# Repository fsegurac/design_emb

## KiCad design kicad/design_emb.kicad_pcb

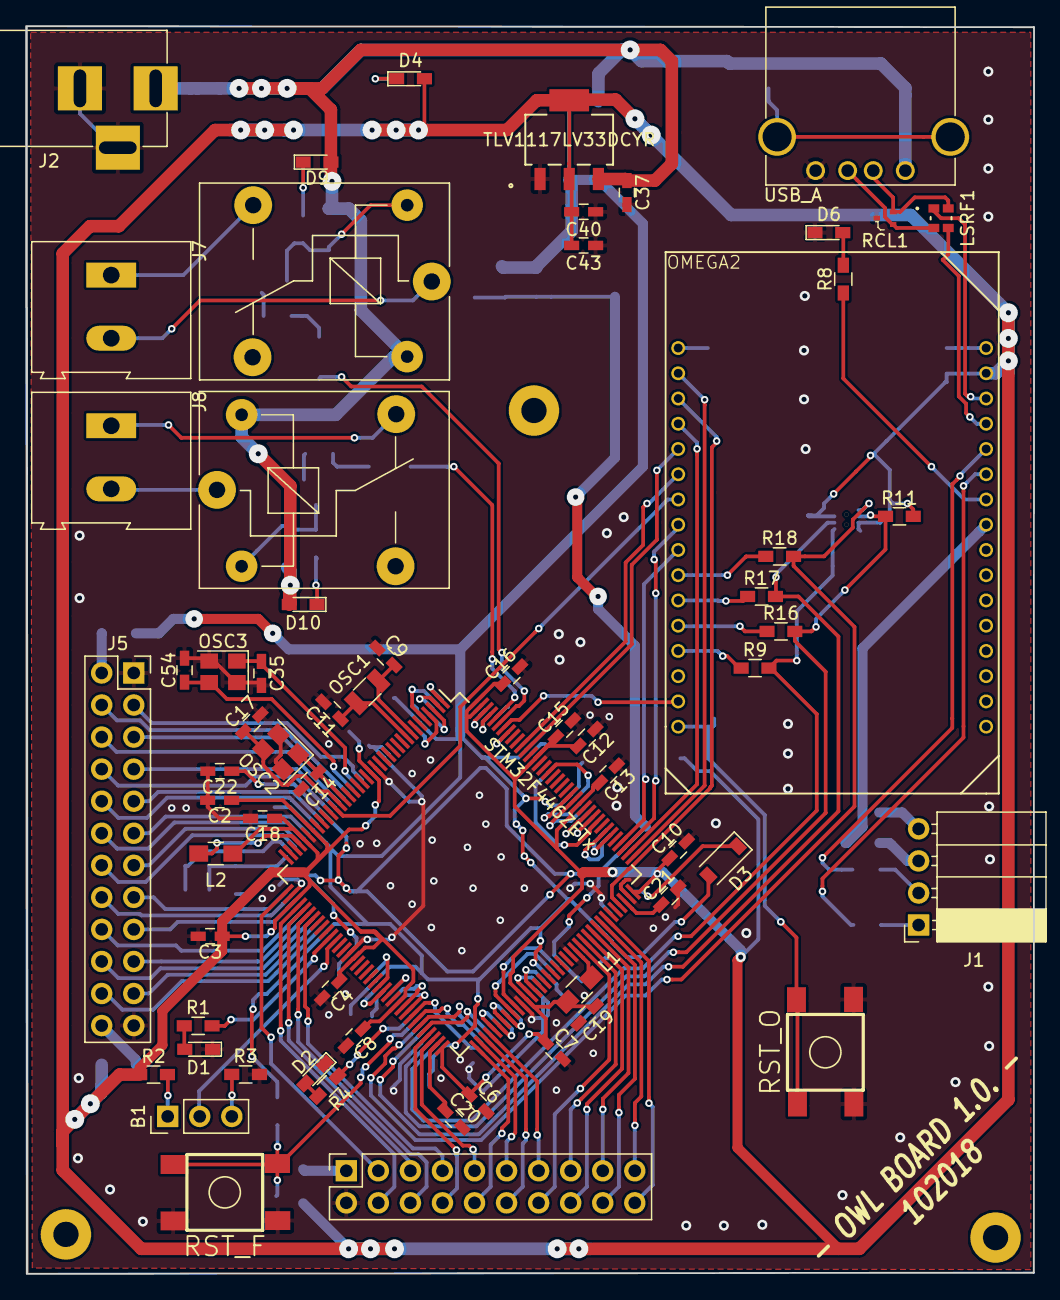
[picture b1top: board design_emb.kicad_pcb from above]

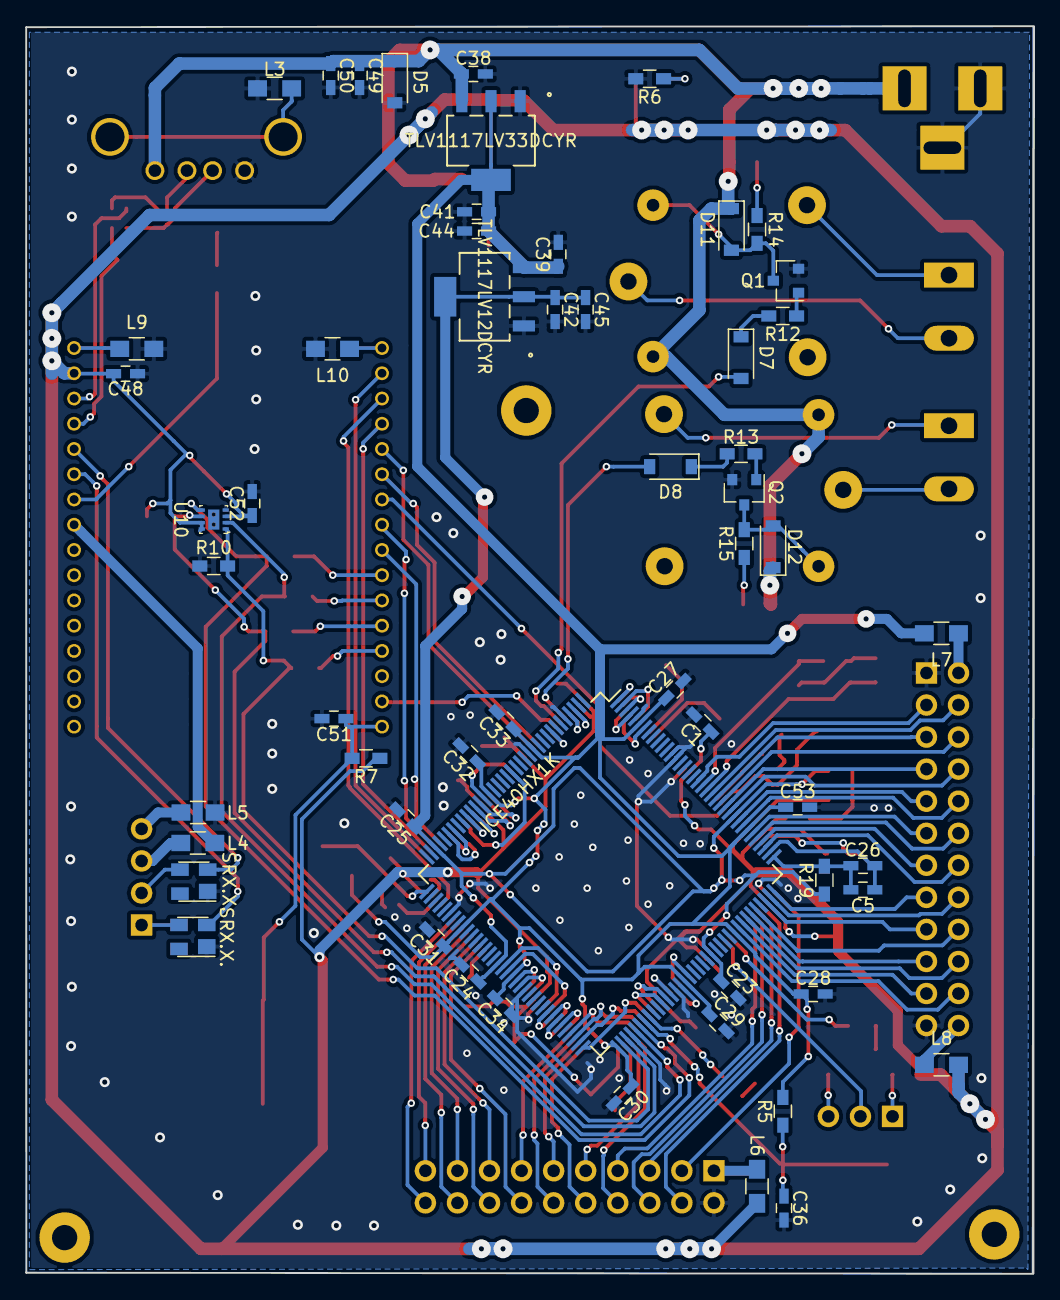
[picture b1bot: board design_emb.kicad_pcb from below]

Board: 2 copper layers, 79.8 x 98.9 mm, 121 parts (56 on the bottom side), 149 nets.

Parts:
B1: Conn_01x03; Pin_Header_Straight_1x03_Pitch2.54mm
C1, C2, C3, C4, C6, C7, C8, C10, C12, C13, C15, C18, C22, C23, C24, C25, C26, C27, C28, C29, C30, C31, C32, C33, C34, C36, C48, C51, C52, C53: 100nF; C_0603_HandSoldering
C5: 10uF; C_0603_HandSoldering
C9, C11: 9pF; C_0603_HandSoldering
C14, C17, C35, C54: 10pF; C_0603_HandSoldering
C16: 4.7uF; C_0603_HandSoldering
C19, C37, C38, C39, C40, C41, C42: 1uF; C_0603_HandSoldering
C20, C21: 2.2uF; C_0603_HandSoldering
C43, C44, C45, C50: 0.1uF; C_0603_HandSoldering
C49: 33uF; C_0603_HandSoldering
D1: LED_PRB; LED_0603_HandSoldering
D2: LED; LED_0603_HandSoldering
D3: 1N5817; D_SOD-123
D4: LED_ON; LED_0603_HandSoldering
D5: D_Scho; D_SOD-123
D6: LED_PROBE; LED_0603_HandSoldering
D7, D8: D_Schottky; D_SOD-123
D9, D10: LED_REL_ON; LED_0603_HandSoldering
D11, D12: D; D_SOD-123
ICE40HX1K: ICE40HX1K; LQFP-144_20x20mm_Pitch0.5mm
J1: Conn_01x04; PinSocket_1x04_P2.54mm_Horizontal
J2: Barrel_Jack; BARREL_JACK
J5: Conn_02x12_Counter_Clockwise; Socket_Strip_Straight_2x12_Pitch2.54mm
J6: Conn_02x10_Counter_Clockwise; Socket_Strip_Straight_2x10_Pitch2.54mm
J7, J8: Screw_Terminal_01x02; TerminalBlock_Altech_AK300-2_P5.00mm
K1, K2: SANYOU_SRD_Form_C; Relay_SPDT_SANYOU_SRD_Series_Form_C
L1, L2: INDUCTOR; L_0805_HandSoldering
L3, L4, L5, L6, L7, L8, L9, L10: L; L_0805_HandSoldering
LSRF1: SRF2012-900YA
OMEGA2: OMEGA2; ONION2
OSC1: 32,768K; Crystal_SMD_3215-2Pin_3.2x1.5mm
OSC2, OSC3: 12MHz; Crystal_SMD_Abracon_ABM8G-4pin_3.2x2.5mm
Q1, Q2: MMBT3904; SOT-23
R1, R4, R6, R8: 1k; R_0603_HandSoldering
R2, R3, R5, R7: 10k; R_0603_HandSoldering
R9, R16, R17, R18, R19: 100; R_0603_HandSoldering
R10, R11: 4.7k; R_0603_HandSoldering
R12, R13: 5,1K; R_0603_HandSoldering
R14, R15: 2,2K; R_0603_HandSoldering
RCL1: RCLAMP0502B; SOT-523
RST_F: SW_Push; TACTILE_SWITCH_6mm
RST_O: SW_Push; TACTILE_SWITCH_6mm
SRX.X., SRX.X.#2: SRX.X.TCT; SOT-143
STM32F446ZETx: STM32F446ZETx; LQFP-144_20x20mm_Pitch0.5mm
U5, U6: TLV1117LV33DCYR
U7: TLV1117LV12DCYR; TLV1117LV33DCYR
U10: S25FL116KOXNFIQ-11; WSON-8_2x2mm
USB_A: USB_A

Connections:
+5VA: C37.1, C38.1, C49.1, C50.1, D5.1, D9.2, D10.2, D11.1, D12.1, J2.1, K1.5, K2.5, U5.3, U6.3, USB_A.1
/3V3_O: L4.2, OMEGA2.25
/RX_OUT: J1.1, SRX.X..3
/SERIAL_RX: OMEGA2.27, SRX.X..2
/SERIAL_TX: OMEGA2.28, SRX.X.#2.2
/Sheet1/BOOT0: OMEGA2.15, STM32F446ZETx.138
/Sheet1/BOOT1: B1.2, STM32F446ZETx.48
/Sheet1/CTRL0: ICE40HX1K.137, STM32F446ZETx.137
/Sheet1/CTRL1: ICE40HX1K.128, STM32F446ZETx.117
/Sheet1/CTRL2: ICE40HX1K.118, STM32F446ZETx.118
/Sheet1/CTRL3: ICE40HX1K.119, STM32F446ZETx.119
/Sheet1/CTRL4: ICE40HX1K.120, STM32F446ZETx.122
/Sheet1/CTRL5: ICE40HX1K.121, STM32F446ZETx.123
/Sheet1/FMCA16: ICE40HX1K.81, STM32F446ZETx.80
/Sheet1/FMCA17: ICE40HX1K.90, STM32F446ZETx.81
/Sheet1/FMCA18: ICE40HX1K.91, STM32F446ZETx.82
/Sheet1/FMCA19: ICE40HX1K.3, STM32F446ZETx.2
/Sheet1/FMCA20: ICE40HX1K.4, STM32F446ZETx.3
/Sheet1/FMCA21: ICE40HX1K.7, STM32F446ZETx.4
/Sheet1/FMCA22: ICE40HX1K.2, STM32F446ZETx.5
/Sheet1/FMCA23: ICE40HX1K.1, STM32F446ZETx.1
/Sheet1/FMCA24: ICE40HX1K.122, STM32F446ZETx.128
/Sheet1/FMCAD0: ICE40HX1K.87, STM32F446ZETx.85
/Sheet1/FMCAD1: ICE40HX1K.88, STM32F446ZETx.86
/Sheet1/FMCAD2: ICE40HX1K.115, STM32F446ZETx.114
/Sheet1/FMCAD3: ICE40HX1K.114, STM32F446ZETx.115
/Sheet1/FMCAD4: ICE40HX1K.56, STM32F446ZETx.58
/Sheet1/FMCAD5: ICE40HX1K.58, STM32F446ZETx.59
/Sheet1/FMCAD6: ICE40HX1K.60, STM32F446ZETx.60
/Sheet1/FMCAD7: ICE40HX1K.61, STM32F446ZETx.63
/Sheet1/FMCAD8: ICE40HX1K.62, STM32F446ZETx.64
/Sheet1/FMCAD9: ICE40HX1K.73, STM32F446ZETx.65
/Sheet1/FMCAD10: ICE40HX1K.74, STM32F446ZETx.66
/Sheet1/FMCAD11: ICE40HX1K.75, STM32F446ZETx.67
/Sheet1/FMCAD12: ICE40HX1K.76, STM32F446ZETx.68
/Sheet1/FMCAD13: ICE40HX1K.78, STM32F446ZETx.77
/Sheet1/FMCAD14: ICE40HX1K.79, STM32F446ZETx.78
/Sheet1/FMCAD15: ICE40HX1K.80, STM32F446ZETx.79
/Sheet1/FMCNBL0: ICE40HX1K.141, STM32F446ZETx.141
/Sheet1/FMCNBL1: ICE40HX1K.142, STM32F446ZETx.142
/Sheet1/JTAG0: OMEGA2.2, STM32F446ZETx.109
/Sheet1/JTAG1: OMEGA2.3, STM32F446ZETx.105
/Sheet1/JTAG2: OMEGA2.4, STM32F446ZETx.110
/Sheet1/JTAG3: OMEGA2.5, STM32F446ZETx.133
/Sheet1/JTAG4: OMEGA2.6, STM32F446ZETx.134
/Sheet1/OSC32_IN: C9.1, OSC1.1, STM32F446ZETx.8
/Sheet1/OSC32_OUT: C11.1, OSC1.2, STM32F446ZETx.9
/Sheet1/OSC_IN: C14.1, OSC2.1, STM32F446ZETx.23
/Sheet1/OSC_OUT: C17.1, OSC2.3, STM32F446ZETx.24
/Sheet1/PROBE: R1.2, STM32F446ZETx.47
/Sheet1/UART4_RX: OMEGA2.9, STM32F446ZETx.112
/Sheet1/UART4_TX: OMEGA2.8, STM32F446ZETx.111
/Sheet1/USR1: J6.3, STM32F446ZETx.37
/Sheet1/USR2: J6.4, STM32F446ZETx.40
/Sheet1/USR3: J6.5, STM32F446ZETx.41
/Sheet1/USR4: J6.6, STM32F446ZETx.42
/Sheet1/USR5: J6.7, STM32F446ZETx.43
/Sheet1/USR6: J6.8, STM32F446ZETx.69
/Sheet1/USR7: J6.9, STM32F446ZETx.70
/Sheet1/USR8: J6.10, STM32F446ZETx.73
/Sheet1/USR9: J6.11, STM32F446ZETx.74
/Sheet1/USR10: J6.12, STM32F446ZETx.75
/Sheet1/USR11: J6.13, STM32F446ZETx.76
/Sheet1/USR12: J6.14, STM32F446ZETx.96
/Sheet1/USR13: J6.15, STM32F446ZETx.97
/Sheet1/USR14: J6.16, STM32F446ZETx.98
/Sheet1/USR15: J6.17, STM32F446ZETx.99
/Sheet1/USR16: J6.18, STM32F446ZETx.100
/Sheet1/USR17: J6.19, STM32F446ZETx.101
/Sheet1/USR18: J6.20, STM32F446ZETx.102
/Sheet1/VCAP1: C20.1, STM32F446ZETx.71
/Sheet1/VCAP2: C21.1, STM32F446ZETx.106
/Sheet1/VDDA: L2.2, STM32F446ZETx.33
/Sheet1/VDDUSB: L1.2, STM32F446ZETx.95
/Sheet2/JNRST: OMEGA2.7, STM32F446ZETx.25
/Sheet2/PROBE: OMEGA2.26, R8.1
/Sheet2/RESET: C51.1, OMEGA2.16, R7.2, RST_O.1
/Sheet2/SPI0: ICE40HX1K.71, R9.2, R10.2, U10.1
/Sheet2/SPI1: ICE40HX1K.70, R11.1, R16.2, U10.6
/Sheet2/SPI2: ICE40HX1K.68, R17.2, U10.2
/Sheet2/SPI3: ICE40HX1K.67, R18.2, U10.5
/Sheet2/USB+: LSRF1.1, OMEGA2.30
/Sheet2/USB-: LSRF1.3, OMEGA2.29
/Sheet4/+1V2_FPGA: C22.1, C23.1, C24.1, C25.1, C42.1, C45.1, ICE40HX1K.27, ICE40HX1K.51, ICE40HX1K.92, ICE40HX1K.111, R19.2, U7.2, U7.4
/Sheet4/+3V3: C1.1, C2.1, C3.1, C4.1, C6.1, C7.1, C8.1, C10.1, C12.1, C13.1, C15.1, C16.1, C18.1, C19.1, C40.1, C43.1, C48.1, C52.1, D4.2, L1.1, L2.1, L6.2, L8.2, OMEGA2.31, R2.1, R7.1, R11.2, STM32F446ZETx.17, STM32F446ZETx.30, STM32F446ZETx.32, STM32F446ZETx.39, STM32F446ZETx.52, STM32F446ZETx.62, STM32F446ZETx.72, STM32F446ZETx.84, STM32F446ZETx.108, STM32F446ZETx.121, STM32F446ZETx.131, STM32F446ZETx.143, STM32F446ZETx.144, U5.2, U5.4, U10.3, U10.7, U10.8
/Sheet4/+3V3_FPGA: C27.1, C28.1, C29.1, C30.1, C31.1, C32.1, C33.1, C34.1, C39.1, C41.1, C44.1, C53.1, D3.2, ICE40HX1K.6, ICE40HX1K.30, ICE40HX1K.46, ICE40HX1K.57, ICE40HX1K.72, ICE40HX1K.89, ICE40HX1K.100, ICE40HX1K.123, ICE40HX1K.133, L7.2, R5.2, U6.2, U6.4, U7.3
/Sheet5/IN_REL1: D7.2, STM32F446ZETx.139
/Sheet5/IN_REL2: D8.2, STM32F446ZETx.140
/TX_IN: J1.2, SRX.X.#2.3
/sheet3/CRESET_B: C36.1, ICE40HX1K.66, R5.1, RST_F.1
/sheet3/GPIO0: ICE40HX1K.19, J5.3
/sheet3/GPIO1: ICE40HX1K.22, J5.4
/sheet3/GPIO2: ICE40HX1K.23, J5.5
/sheet3/GPIO3: ICE40HX1K.24, J5.6
/sheet3/GPIO4: ICE40HX1K.25, J5.7
/sheet3/GPIO5: ICE40HX1K.26, J5.8
/sheet3/GPIO6: ICE40HX1K.28, J5.9
/sheet3/GPIO7: ICE40HX1K.29, J5.10
/sheet3/GPIO8: ICE40HX1K.31, J5.11
/sheet3/GPIO9: ICE40HX1K.32, J5.12
/sheet3/GPIO10: ICE40HX1K.33, J5.13
/sheet3/GPIO11: ICE40HX1K.34, J5.14
/sheet3/GPIO12: ICE40HX1K.37, J5.15
/sheet3/GPIO13: ICE40HX1K.38, J5.16
/sheet3/GPIO14: ICE40HX1K.39, J5.17
/sheet3/GPIO15: ICE40HX1K.41, J5.18
/sheet3/GPIO16: ICE40HX1K.42, J5.19
/sheet3/GPIO17: ICE40HX1K.43, J5.20
/sheet3/GPIO18: ICE40HX1K.44, J5.21
/sheet3/GPIO19: ICE40HX1K.45, J5.22
/sheet3/OSC_IN: C35.1, ICE40HX1K.20, OSC3.1
/sheet3/OSC_OUT: C54.1, ICE40HX1K.21, OSC3.3
/sheet3/PLLGND: C5.2, C26.2, ICE40HX1K.35
/sheet3/VCCPLL: C5.1, C26.1, ICE40HX1K.36, R19.1
GND: C1.2, C2.2, C3.2, C4.2, C6.2, C7.2, C8.2, C9.2, C10.2, C11.2, C12.2, C13.2, C14.2, C15.2, C16.2, C17.2, C18.2, C19.2, C20.2, C21.2, C22.2, C23.2, C24.2, C25.2, C27.2, C28.2, C29.2, C30.2, C31.2, C32.2, C33.2, C34.2, C35.2, C36.2, C37.2, C38.2, C39.2, C40.2, C41.2, C42.2, C43.2, C44.2, C45.2, C48.2, C49.2, C50.2, C51.2, C52.2, C53.2, C54.2, D1.1, D2.1, D5.2, D6.1, ICE40HX1K.5, ICE40HX1K.13, ICE40HX1K.14, ICE40HX1K.59, ICE40HX1K.69, ICE40HX1K.86, ICE40HX1K.103, ICE40HX1K.132, ICE40HX1K.140, J2.2, J2.3, J5.1, J5.23, J6.2, L3.2, L5.2, L9.2, L10.2, OSC2.2, OSC2.4, OSC3.2, OSC3.4, Q1.2, Q2.2, R3.2, R6.2, R10.1, RCL1.3, RST_F.2, RST_O.2, SRX.X..1, SRX.X.#2.1, STM32F446ZETx.16, STM32F446ZETx.31, STM32F446ZETx.38, STM32F446ZETx.51, STM32F446ZETx.61, STM32F446ZETx.83, STM32F446ZETx.94, STM32F446ZETx.107, STM32F446ZETx.120, STM32F446ZETx.130, U5.1, U6.1, U7.1, U10.4, USB_A.4
unnamed: D1.2, R1.1
unnamed: D2.2, R4.2
unnamed: D3.1, ICE40HX1K.108
unnamed: D4.1, R6.1
unnamed: D6.2, R8.2
unnamed: D7.1, R12.2
unnamed: D8.1, R13.2
unnamed: D9.1, R14.1
unnamed: D10.1, R15.1
unnamed: D11.2, K1.2, Q1.3, R14.2
unnamed: D12.2, K2.2, Q2.3, R15.2
unnamed: J1.3, L4.1
unnamed: J1.4, L5.1
unnamed: LSRF1.4, RCL1.2, USB_A.2
unnamed: LSRF1.2, RCL1.1, USB_A.3
unnamed: L3.1, USB_A.5
unnamed: B1.1, R2.2
unnamed: B1.3, R3.1
unnamed: J5.2, L7.1
unnamed: J5.24, L8.1
unnamed: J6.1, L6.1
unnamed: J7.1, K1.3
unnamed: J7.2, K1.1
unnamed: J8.1, K2.4
unnamed: J8.2, K2.1
unnamed: L9.1, OMEGA2.32
unnamed: L10.1, OMEGA2.1
unnamed: OMEGA2.10, R18.1
unnamed: OMEGA2.11, R17.1
unnamed: OMEGA2.12, R16.1
unnamed: OMEGA2.13, R9.1
unnamed: Q1.1, R12.1
unnamed: Q2.1, R13.1
unnamed: ICE40HX1K.65, R4.1

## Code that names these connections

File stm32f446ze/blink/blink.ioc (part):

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Mcu.Name=STM32F446Z(C-E)Tx
Mcu.Package=LQFP144
Mcu.UserName=STM32F446ZETx
PA13.Mode=JTAG_5_pins
PA13.Signal=SYS_JTMS-SWDIO
PA14.Mode=JTAG_5_pins
PA14.Signal=SYS_JTCK-SWCLK
PA15.Mode=JTAG_5_pins
PA15.Signal=SYS_JTDI
PB1.GPIOParameters=GPIO_Speed,PinState,GPIO_PuPd,GPIO_ModeDefaultOutputPP
PB1.GPIO_ModeDefaultOutputPP=GPIO_MODE_OUTPUT_PP
PB1.GPIO_PuPd=GPIO_PULLUP
PB1.GPIO_Speed=GPIO_SPEED_FREQ_HIGH
PB1.PinState=GPIO_PIN_SET
PB1.Signal=GPIO_Output
PB3.Mode=JTAG_5_pins
PB3.Signal=SYS_JTDO-SWO
PB4.Mode=JTAG_5_pins
PB4.Signal=SYS_JTRST
PC14-OSC32_IN.Mode=LSE-External-Oscillator
PC14-OSC32_IN.Signal=RCC_OSC32_IN
PC15-OSC32_OUT.Mode=LSE-External-Oscillator
PC15-OSC32_OUT.Signal=RCC_OSC32_OUT
PH0-OSC_IN.Mode=HSE-External-Oscillator
PH0-OSC_IN.Signal=RCC_OSC_IN
PH1-OSC_OUT.Mode=HSE-External-Oscillator
PH1-OSC_OUT.Signal=RCC_OSC_OUT
RCC.HSE_VALUE=12000000
board=custom

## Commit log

2018-08-23 init
2018-08-23 init 1.0
2018-08-24 creacion bus y libreria
2018-08-27 libreria kicad-4
2018-08-27 actualización kicad
2018-08-27 creacion bus FMC
2018-08-28 creacion buses y alimentacion .sch
2018-08-29 modificaciones stm32 y adición de Omega-2
2018-08-30 comunicación serial usuario
2018-08-30 osciladores stm32
2018-09-01 Borrado de archivos .bck
2018-09-01 borrado archivos .bak
2018-09-01 modificacion .gitignore
2018-09-01 .gitignore OMEGA2sch.bak
2018-09-01 design_emb.sch
2018-09-02 ignorar archivo design_emb-cache.lib
2018-09-02 creacion simbolo fpga (3 bancos)
2018-09-02 creación completa símbolo fpga ice40hx1k
2018-09-04 capacitores desacople stm32
2018-09-04 reconfiguracion capacitores de desacople
2018-09-04 link V. regulator
2018-09-11 link regulador stm
2018-09-11 regulador 3v3
2018-09-12 kicad/fpga.sch
2018-09-12 reguladores y conexión a stm32
2018-09-12 comunicación omega2 y stm32
2018-09-12 usb omega2
2018-09-13 leds de prueba
2018-09-13 anotaciones
2018-09-19 footprints resistencias y condensadores
2018-09-24 footprints y JTAG
2018-09-26 OMEGA2sch.sch
2018-09-26 arreglo huella fpga
2018-09-26 STM32F446ZETx.sch
2018-09-26 boot1 jack
2018-09-26 footprints
2018-09-26 fpga.sch
2018-09-27 perifericos stm32
2018-10-02 corrección footprints
2018-10-03 fp-lib-table
2018-10-03 Flash.bck
2018-10-03 dgk_footprints.pretty/
2018-10-03 buses JTAG, FMC_AD y CTRL
2018-10-03 design_emb.bak
2018-10-04 bus SPI, FMC_A Y FMC_NBL
2018-10-04 design_emb.net
2018-10-04 design_emb.kicad_pcb
2018-10-04 design_emb.ses
2018-10-04 arreglo pines FPGA compatibilidad STM32
2018-10-04 ruteo
2018-10-05 footprint sw_push
2018-10-11 plano de tierra y modificación de señales
2018-10-16 modificación alimentación PLL fpga
2018-10-18 soportes mecánicos y osc fpga
2018-10-19 correcciones silk
2018-10-19 cambio osc1 stm32
2018-10-19 datasheet diodos schottky
2018-10-19 corrección errores DRC
2018-10-20 vías de GND
2018-10-20 cambio socket fpga
2019-02-14 gerbers
2019-02-14 archivos necesarios en Omega2
2019-02-14 archivos de programacion stm32f446
2019-03-18 OmegaDone.png
2019-03-18 D263.png
2019-03-18 STM.png
2019-03-18 JTAGcnfig1.png
2019-03-18 Yosys.png
2019-03-18 Arachne.png
2019-03-18 correcciones pcb
2019-03-18 Board.png

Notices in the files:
parts and their libraries:
Copyright 2016 Accelerated Designs. All rights reserved.
